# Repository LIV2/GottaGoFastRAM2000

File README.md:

# GottaGoFastRAM2000 8MB Autoconfig Fast RAM

This is an 8MB Autoconfig Fast RAM for the Amiga 2000 

Special thanks to [GadgetUK164](https://www.youtube.com/user/GadgetUK164) and sparxUK for their help testing this.

## Table of contents
1. [Status](#status)
1. [Features](#features)
1. [Firmware](#firmware)
1. [PCB Ordering](#ordering-pcbs)
1. [Jumpers](#jumpers)
1. [Bill of materials](#bill-of-materials)
1. [Troubleshooting](#troubleshooting)

## Status

This is tested and working

## Features

* 8MB of Fast RAM
* Auto-sizing - The RAM board will coexist with other devices by autosizing to fit the remaining free Zorro II memory space

## Firmware

There are two different firmwares available for this card.
1. [Standard autosizing](https://github.com/LIV2/GottaGoFastRAM2000/raw/master/Binary/XC9572XL/gottagofast2000.jed) - This Firmware will autosize trying in this order: 8MB -> 4MB -> 2MB -> 1MB until it can fit in the remaining space
2. [6MB autosizing](https://github.com/LIV2/GottaGoFastRAM2000/raw/master/Binary/XC9572XL/gottagofast2000-6MB.jed) - This will try to offer 8MB then 6MB (in a block of 2MB + 4MB) to maximize space i.e when using a bridgeboard that needs 512K itself

## PCB Ordering

For best results the boards should be manufactured with the "Gold Fingers" option so that the edge connector will survive many insertion/removal cycles

## Jumpers

4MB: Forces the board to appear as a 4MB board rather than 8MB

### Bill of materials

|Component|Location|QTY|Link|Note|
|---------|--------|---|----|----|
|LM1117-3.3 SOT-223|U1|1|[Mouser](https://www.mouser.com/ProductDetail/926-LM1117IMP3.3NOPB)||
|XC9572XL-10TQ100C|U5|1|[Mouser](https://www.mouser.com/ProductDetail/217-C9572XL-10TQ100C)|Can be substituted with XC95144XL-10-TQ100|
|74LS245 SOIC|U3,U4|2|[Mouser](https://www.mouser.com/ProductDetail/595-SN74LS245DWR)||
|74LVC2G07|U2|1|[Mouser](https://www.mouser.com/ProductDetail/595-SN74LVC2G07DBVR)|*Optional - See below|
|5v 1MBx16 DRAM, SOJ-42  i.e  <br/>K4E151611<br/>K4F151611<br/>MT4C1M16E5<br/>GM71C18163C<br/>AS4C1M16E5 etc.|U6,U7,U8,U9|4|Aliexpress, Ebay etc|Other parts may be compatible so long as they meet these specs: 5V, SOJ-42, 1K Refresh, 1024 row x 1024 column x 16 bits|
|0.1uF Ceramic capacitor, 0805|C4-25|22|[Mouser](https://www.mouser.com/ProductDetail/581-08055C104K)||
|10uF Ceramic capacitor, 1206|C2,C3|2|[Mouser](https://www.mouser.com/ProductDetail/80-C1206C106K4R)||
|100uF Electrolytic Capacitor|C1|1|[Mouser](https://www.mouser.com/ProductDetail/667-16SEPC100M)||
|10K Resistor, 0805|R1|1|[Mouser](https://www.mouser.com/ProductDetail/754-RR1220P-103D)|

\* U2 buffers the cards generated DTACK and OVR signals - In a pinch this can be left out but you will run into problems with the A2091 and some other devices so it is best to fit this and save yourself the headache

## Troubleshooting
* **Problem**: System does not boot, the power LED does not change brightness  
  **Solution**: Possible incorrect orientation/faulty ic in U2 - check orientation and/or remove this IC and try again

* **Problem**: My bridgeboard doesn't work when this card is installed  
  **Solution**: The bridgeboard needs 512K of the 8MB expansion space for its own use, you will need to move the ram board to the leftmost slot and I recommend flashing the [6MB Firmware](https://github.com/LIV2/GottaGoFastRAM2000/raw/master/Binary/XC9572XL/gottagofast2000-6MB.jed) to maximise the amount of memory offered when used with the bridgeboard

* **Problem**: My system is unstable / graphical corruption when using this board but it passes a memory test in ATK/DiagROM etc  
  **Solution**: Check that your Amiga 2000 has the correct buffers installed in U600-605. U600,601,603,604 __must__ be 74LS245 and U602/605 should be 74ALS245 but might be 74LS245 in some A2000 revisions.  
  If you have used anything else (like 74HCT245) for these you will run into issues with this board and many others.

* **Problem**: When used with a bridgeboard/other cards I get a gray screen telling me the card has been "SHUT"  
  **Solution**: Some other board is using some of the 8MB space, so the card will be told to shutup and will reappear offering 4MB then 2, 1 etc.  
  On Kick 1.3-3.1 the system will not alert you to this happening and will continue to boot (this is used to do the autosizing) but newer versions "helpfully" tell you about this condition.  
  If using one of these newer kickstart versions with a Bridgeboard I'd recommend flashing the [6MB Firmware](https://github.com/LIV2/GottaGoFastRAM2000/raw/master/Binary/XC9572XL/gottagofast2000-6MB.jed)  
  Another option would be to write the firmware to offer multiple 2MB blocks until it is shut up which unfortunately doesn't work, because Kickstart 1.3-3.1 will throw a yellow screen if the last board in the chain was shut up, and newer versions will throw the gray screen telling us the board has been shut-up.
  
* **Problem**: With the board installed I get a red screen saying that this board is defective  
  **Solution**: This usually means that one of the RAM chips are faulty or there could be bad soldering.  
  Remove all other Zorro cards, boot up [ATK](https://github.com/keirf/amiga-stuff/releases) or Diagrom and do a manual memory test with the individual ranges listed in the memory map below.  
  Consult the memory map below to figure out which RAM chip is being reported faulty.
  If the same bits are reported as faulty across multiple of the address ranges check for bad soldering around the RAM chips and the buffers at U3&U4.  

### Memory Map
|Address range|Chip|
|-------------|----|
|200000-3FFFFF|U6|
|400000-5FFFFF|U7|
|600000-7FFFFF|U8|
|800000-9FFFFF|U9|

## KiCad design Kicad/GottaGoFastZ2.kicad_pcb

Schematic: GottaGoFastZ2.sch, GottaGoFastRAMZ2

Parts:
C1: 100u; CP_Radial_D5.0mm_P2.50mm
C2, C3: 10u; C_1206_3216Metric_Pad1.33x1.80mm_HandSolder
C4, C5, C6, C7, C8, C9, C10, C11, C12, C13, C14, C15, C16, C17, C18, C19, C20, C21, C22, C23, C24, C25: 0.1u; C_0805_2012Metric_Pad1.18x1.45mm_HandSolder
CON1: Zorro2; Zorro2-CardEdge
J1: 4MB; PinHeader_1x02_P2.54mm_Vertical
J2: Conn_01x06_Male; PinHeader_1x06_P2.54mm_Vertical
R1: 10K; R_0805_2012Metric_Pad1.20x1.40mm_HandSolder
U1: LM1117-3.3; SOT-223-3_TabPin2
U2: 74LVC2G07; SOT-23-6
U3, U4: 74LS245; SOIC-20W_7.5x12.8mm_P1.27mm
U5: XC9572XL-TQ100; TQFP-100_14x14mm_P0.5mm
U6, U7, U8, U9: HYB5118160BSJ; SOJ-42-LongPads

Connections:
+3V3: C3.1, C4.1, C5.1, C8.1, C11.1, C14.1, C19.1, C22.1, C25.1, J2.6, R1.1, U1.2 (VO), U2.5, U5.5 (VCC), U5.26 (VCCIO), U5.38 (VCCIO), U5.51 (VCCIO), U5.57 (VCC), U5.88 (VCCIO), U5.98 (VCC)
+5V: C1.1, C2.1, C6.1, C7.1, C9.1, C10.1, C12.1, C13.1, C15.1, C16.1, C17.1, C18.1, C20.1, C21.1, C23.1, C24.1, CON1.5 (+5), CON1.6 (+5), U1.3 (VI), U3.20 (VCC), U4.20 (VCC), U6.1 (VCC), U6.6 (VCC), U6.21 (VCC), U7.1 (VCC), U7.6 (VCC), U7.21 (VCC), U8.1 (VCC), U8.6 (VCC), U8.21 (VCC), U9.1 (VCC), U9.6 (VCC), U9.21 (VCC)
/4MB: J1.1, R1.2, U5.94
/A1: CON1.29 (A1), U5.59
/A2: CON1.27 (A2), U5.61
/A3: CON1.26 (A3), U5.64
/A4: CON1.24 (A4), U5.66
/A5: CON1.21 (A5), U5.67
/A6: CON1.23 (A6), U5.65
/A7: CON1.28 (A7), U5.63
/A8: CON1.30 (A8), U5.60
/A9: CON1.32 (A9), U5.58
/A10: CON1.34 (A10), U5.56
/A11: CON1.36 (A11), U5.55
/A12: CON1.38 (A12), U5.54
/A13: CON1.39 (A13), U5.53
/A14: CON1.41 (A14), U5.52
/A15: CON1.43 (A15), U5.50
/A16: CON1.45 (A16), U5.42
/A17: CON1.47 (A17), U5.41
/A18: CON1.52 (A18), U5.40
/A19: CON1.54 (A19), U5.39
/A20: CON1.56 (A20), U5.37
/A21: CON1.58 (A21), U5.36
/A22: CON1.57 (A22), U5.35
/A23: CON1.59 (A23), U5.33
/BD0: U3.2 (A0), U6.10 (D8), U7.10 (D8), U8.10 (D8), U9.10 (D8)
/BD1: U3.3 (A1), U6.9 (D7), U7.9 (D7), U8.9 (D7), U9.9 (D7)
/BD2: U3.4 (A2), U6.8 (D6), U7.8 (D6), U8.8 (D6), U9.8 (D6)
/BD3: U3.5 (A3), U6.7 (D5), U7.7 (D5), U8.7 (D5), U9.7 (D5)
/BD4: U3.6 (A4), U6.5 (D4), U7.5 (D4), U8.5 (D4), U9.5 (D4)
/BD5: U3.9 (A7), U6.2 (D1), U7.2 (D1), U8.2 (D1), U9.2 (D1)
/BD6: U3.8 (A6), U6.3 (D2), U7.3 (D2), U8.3 (D2), U9.3 (D2)
/BD7: U3.7 (A5), U6.4 (D3), U7.4 (D3), U8.4 (D3), U9.4 (D3)
/BD8: U4.9 (A7), U6.33 (D9), U7.33 (D9), U8.33 (D9), U9.33 (D9)
/BD9: U4.8 (A6), U6.34 (D10), U7.34 (D10), U8.34 (D10), U9.34 (D10)
/BD10: U4.7 (A5), U6.35 (D11), U7.35 (D11), U8.35 (D11), U9.35 (D11)
/BD11: U4.6 (A4), U6.36 (D12), U7.36 (D12), U8.36 (D12), U9.36 (D12)
/BD12: U4.5 (A3), U5.3 (I/O/GTS1), U6.38 (D13), U7.38 (D13), U8.38 (D13), U9.38 (D13)
/BD13: U4.4 (A2), U5.1 (I/O/GTS3), U6.39 (D14), U7.39 (D14), U8.39 (D14), U9.39 (D14)
/BD14: U4.3 (A1), U5.97, U6.40 (D15), U7.40 (D15), U8.40 (D15), U9.40 (D15)
/BD15: U4.2 (A0), U5.96, U6.41 (D16), U7.41 (D16), U8.41 (D16), U9.41 (D16)
/B~DTACK: CON1.66 (~DTACK), U2.4
/B~OVR: CON1.17 (~OVR), U2.6
/CDAC: CON1.15 (CDAC), U5.72
/D0: CON1.75 (D0), U3.18 (B0)
/D1: CON1.77 (D1), U3.17 (B1)
/D2: CON1.79 (D2), U3.16 (B2)
/D3: CON1.81 (D3), U3.15 (B3)
/D4: CON1.83 (D4), U3.14 (B4)
/D5: CON1.86 (D5), U3.11 (B7)
/D6: CON1.84 (D6), U3.12 (B6)
/D7: CON1.82 (D7), U3.13 (B5)
/D8: CON1.80 (D8), U4.11 (B7)
/D9: CON1.78 (D9), U4.12 (B6)
/D10: CON1.76 (D10), U4.13 (B5)
/D11: CON1.71 (D11), U4.14 (B4)
/D12: CON1.69 (D12), U4.15 (B3)
/D13: CON1.67 (D13), U4.16 (B2)
/D14: CON1.65 (D14), U4.17 (B1)
/D15: CON1.63 (D15), U4.18 (B0)
/DOE: CON1.93 (DOE), U5.95
/MA0: U5.17, U6.17 (A0), U7.17 (A0), U8.17 (A0), U9.17 (A0)
/MA1: U5.20, U6.18 (A1), U7.18 (A1), U8.18 (A1), U9.18 (A1)
/MA2: U5.23 (I/O/GCK2), U6.19 (A2), U7.19 (A2), U8.19 (A2), U9.19 (A2)
/MA3: U5.27 (I/O/GCK3), U6.20 (A3), U7.20 (A3), U8.20 (A3), U9.20 (A3)
/MA4: U5.25, U6.23 (A4), U7.23 (A4), U8.23 (A4), U9.23 (A4)
/MA5: U5.22 (I/O/GCK1), U6.24 (A5), U7.24 (A5), U8.24 (A5), U9.24 (A5)
/MA6: U5.18, U6.25 (A6), U7.25 (A6), U8.25 (A6), U9.25 (A6)
/MA7: U5.16, U6.26 (A7), U7.26 (A7), U8.26 (A7), U9.26 (A7)
/MA8: U5.15, U6.27 (A8), U7.27 (A8), U8.27 (A8), U9.27 (A8)
/MA9: U5.13, U6.28 (A9), U7.28 (A9), U8.28 (A9), U9.28 (A9)
/READ: CON1.68 (READ), U3.1 (A->B), U4.1 (A->B), U5.32
/TCK: J2.4, U5.48 (TCK)
/TDI: J2.2, U5.45 (TDI)
/TDO: J2.3, U5.83 (TDO)
/TMS: J2.1, U5.47 (TMS)
/~AS: CON1.74 (~AS), U5.28
/~BEER: CON1.46 (~BEER), U5.49
/~BUFOE: U3.19 (CE), U4.19 (CE), U5.76
/~C1: CON1.16 (~C1), U5.71
/~C3: CON1.14 (~C3), U5.74
/~CFGIN: CON1.12 (~CFGIN), U5.77
/~CFGOUT: CON1.11 (~CFGOUT), U5.78
/~DTACK: U2.3, U5.68
/~LCAS: U5.6, U6.31 (LCAS), U7.31 (LCAS), U8.31 (LCAS), U9.31 (LCAS)
/~LDS: CON1.70 (~LDS), U5.30
/~MEMWR: U5.9, U6.13 (WE), U7.13 (WE), U8.13 (WE), U9.13 (WE)
/~OVR: U2.1, U5.70
/~RAS1: U5.4 (I/O/GTS2), U6.14 (RAS)
/~RAS2: U5.10, U7.14 (RAS)
/~RAS3: U5.11, U8.14 (RAS)
/~RAS4: U5.14, U9.14 (RAS)
/~RESET: CON1.94 (~BUSRST), U5.99 (I/O/GSR)
/~SLAVE: CON1.9 (~SLAVE), U5.79
/~UCAS: U5.8, U6.30 (UCAS), U7.30 (UCAS), U8.30 (UCAS), U9.30 (UCAS)
/~UDS: CON1.72 (~UDS), U5.29
GND: C1.2, C2.2, C3.2, C4.2, C5.2, C6.2, C7.2, C8.2, C9.2, C10.2, C11.2, C12.2, C13.2, C14.2, C15.2, C16.2, C17.2, C18.2, C19.2, C20.2, C21.2, C22.2, C23.2, C24.2, C25.2, CON1.1 (GND), CON1.2 (GND), CON1.3 (GND), CON1.4 (GND), CON1.13 (GND), CON1.25 (GND), CON1.37 (GND), CON1.49 (GND), CON1.61 (GND), CON1.73 (GND), CON1.85 (GND), CON1.87 (GND), CON1.88 (GND), CON1.89 (GND), CON1.90 (GND), CON1.91 (GND), CON1.99 (GND), CON1.100 (GND), J1.2, J2.5, U1.1 (GND), U2.2, U3.10 (GND), U4.10 (GND), U5.21 (GND), U5.31 (GND), U5.44 (GND), U5.62 (GND), U5.69 (GND), U5.75 (GND), U5.84 (GND), U5.100 (GND), U6.22 (GND), U6.29 (OE), U6.37 (GND), U6.42 (GND), U7.22 (GND), U7.29 (OE), U7.37 (GND), U7.42 (GND), U8.22 (GND), U8.29 (OE), U8.37 (GND), U8.42 (GND), U9.22 (GND), U9.29 (OE), U9.37 (GND), U9.42 (GND)

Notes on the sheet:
RAM decoupling
JTAG
CPLD decoupling
Open collector buffer DTACK/OVR need strong drive

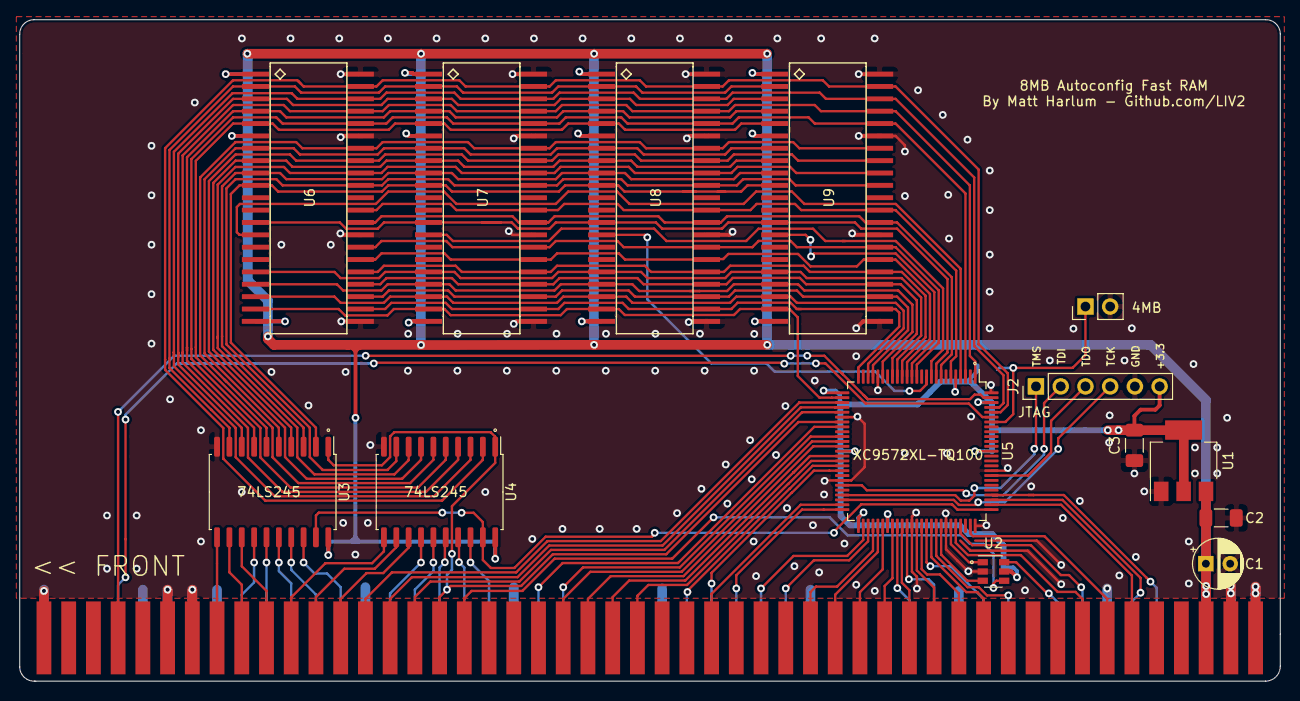
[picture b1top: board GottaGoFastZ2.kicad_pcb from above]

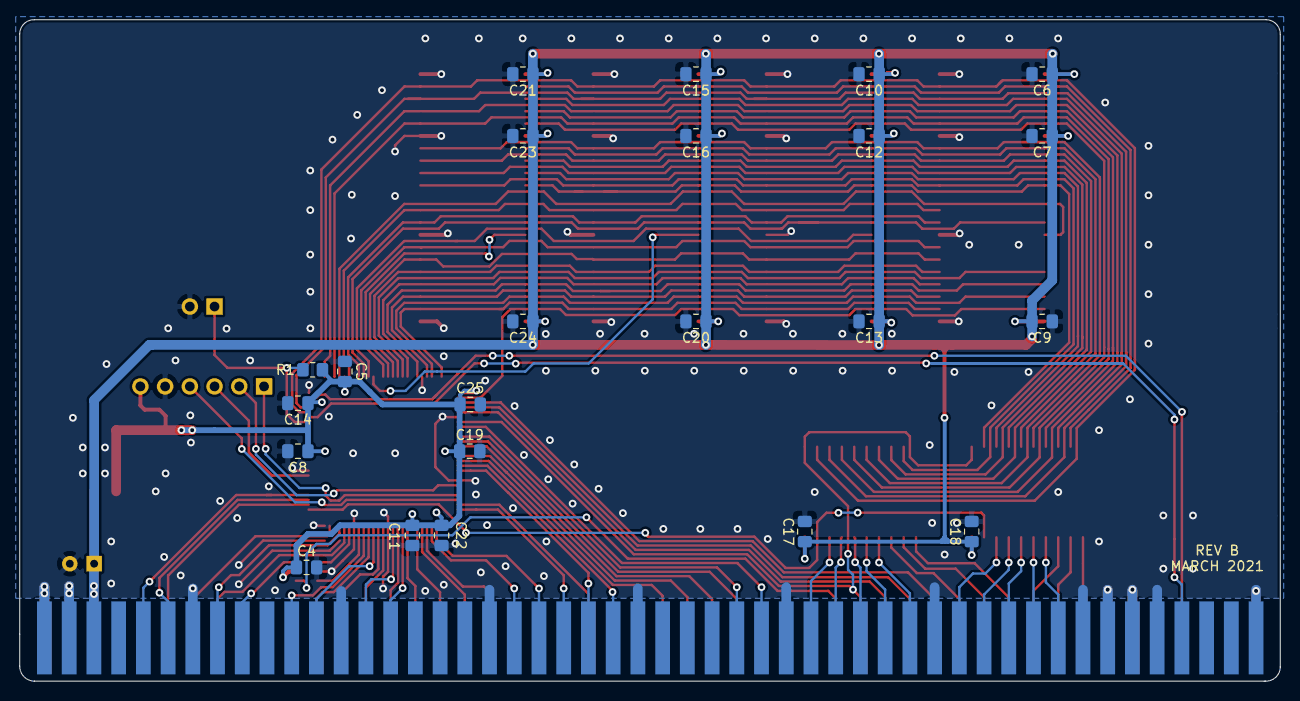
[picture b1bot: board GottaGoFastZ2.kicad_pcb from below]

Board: 2 copper layers, 129.5 x 67.9 mm, 38 parts (23 on the bottom side), 98 nets.

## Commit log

2021-05-20 Initial Public release
2021-05-20 Update copyright date, Add JED file and update README
2021-06-15 Fixup BOM
    Add R1
    Correct P/N for LS245's
2021-07-14 Add Makefile
2021-07-15 Fixup makefile flashing
2021-07-25 Fixup 6MB option, fix Makefile line endings
2021-07-25 Make DTACK synchronous
    * DTACK synchronous to system clock
    * DTACK generated in-phase with DOE
2021-08-23 Expand on DTACK generation comments
2021-08-29 Hold off DTACK until refresh complete
2022-01-07 Bugfixes * Change slew to slow * Make sure autoconfig_cycle is held through the whole cycle instead of releasing immediately
2022-01-12 Update makefile
2022-02-13 Add git revision to Serial number
2022-02-13 When jumpered for 4MB attach the other 4MB to Ranger + A0-BE
2022-04-02 Update README with notes about u2
2022-04-02 Update README: Add more ram types
2022-04-03 Add 6MB build for bridgeboards
2022-04-03 Add note about Zorro Buffers
2022-04-04 Make the 6MB option start at 6MB instead of 8...
2022-04-04 Clarify reasoning for DTACK holdoff
2022-05-25 Add XC95144XL as a substitute for the CPLD
2022-05-25 Add memory layout to aid troubleshooting
2022-05-26 Fixup links to firmware in README
2023-04-15 Switch to OHR assigned autoconfig id
2023-04-15 Add binary builds
2023-04-15 Add github release automation
2024-01-24 README: Fixup typo - thanks @reinauer
2026-03-15 Add note to BOM for DRAM to assist in selecting substitutes
